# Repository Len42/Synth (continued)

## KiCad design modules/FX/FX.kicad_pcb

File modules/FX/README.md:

# Digital Effects Module

## 8HP Eurorack Module

### Features
- Chorus, echo, or plate reverb effect
- Stereo outputs
- Lighted pushbutton for tap tempo
- Uses an [Accu-Bell Effector](https://www.tubesandmore.com/sites/default/files/associated_files/p-r-abe.pdf) DSP module

### Notes
Chorus and reverb effects are stereo; echo is mono, output to both channels.

I wanted the DSP module to lie flat on the PCB so I used a right-angle socket header connector, but the connector's pins are too short so it ended up sitting at an angle:

The DSP module could be soldered directly to the PCB instead, so that it sticks out vertically.

PCB layouts are provided in KiCad and gerber formats. A PCB layout for a drilled front panel is also included.

The PCBs that I used can be ordered from OSH Park. The designs are here:
- [Front panel](https://oshpark.com/shared_projects/IcfnjVSe)
- [Controls board](https://oshpark.com/shared_projects/3NuuYXm0)
- [Main board](https://oshpark.com/shared_projects/yNs2Zlux)

Please note that I am a hobbyist, not a trained electronics engineer. No guarantees!

### Software Used

* [KiCad](https://www.kicad.org/) 6.0.8

<hr /><div><div style="float:left; padding-right:10px;"></div><div style="xfloat:left; padding-left:10px;"><br />© 2022 Len Popp CC BY<br />This work is licensed under a <a rel="license" href="http://creativecommons.org/licenses/by/4.0/">Creative Commons Attribution 4.0 International License</a>.</div></div>

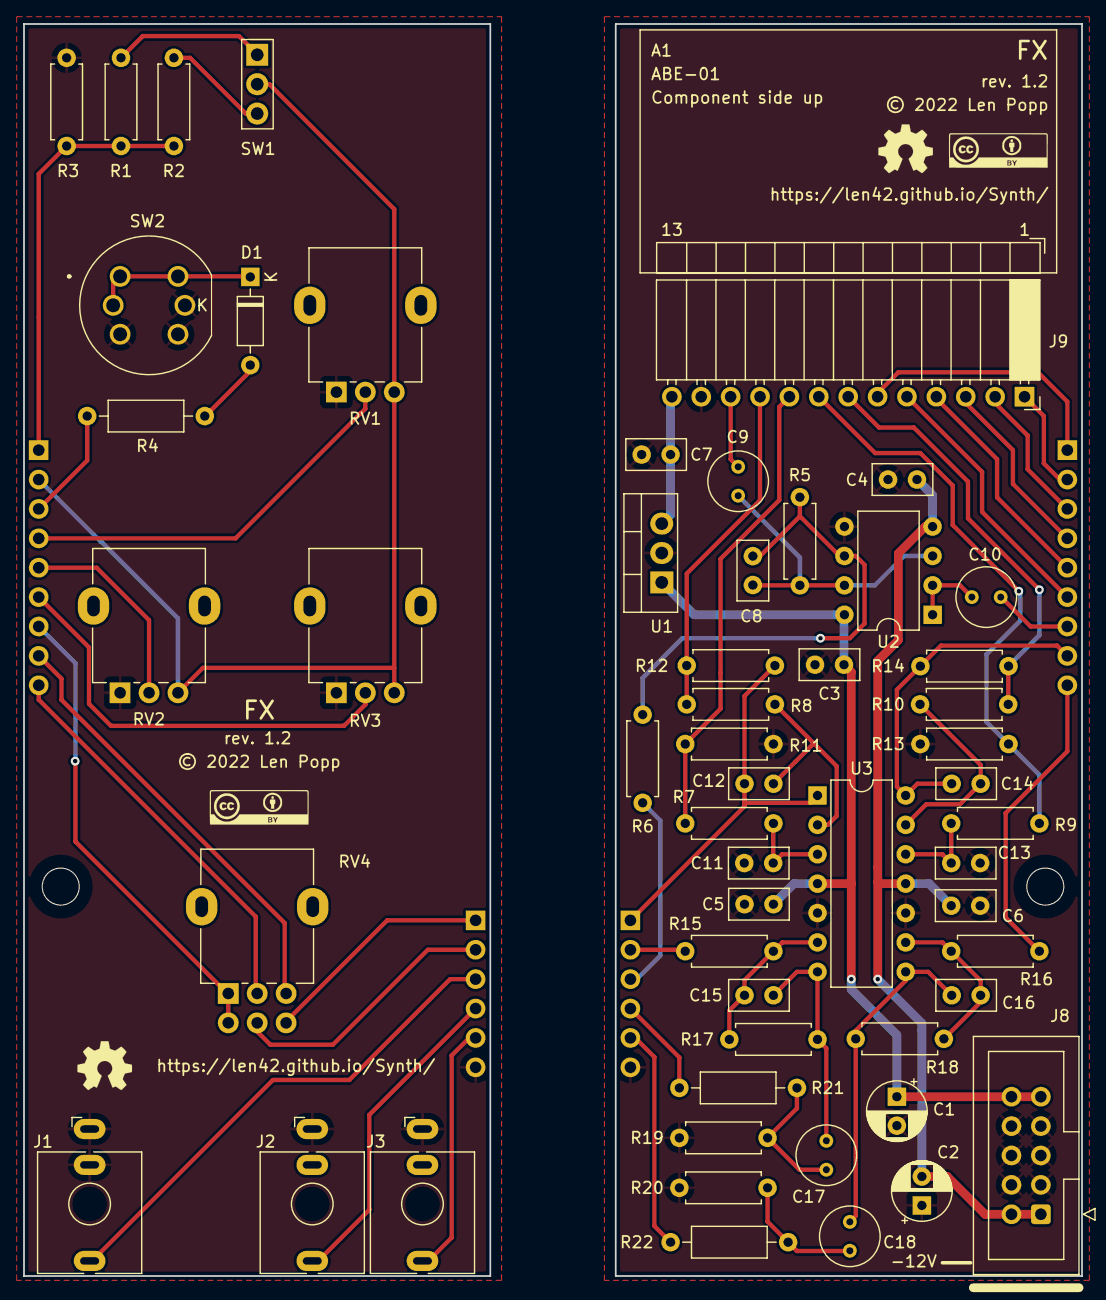
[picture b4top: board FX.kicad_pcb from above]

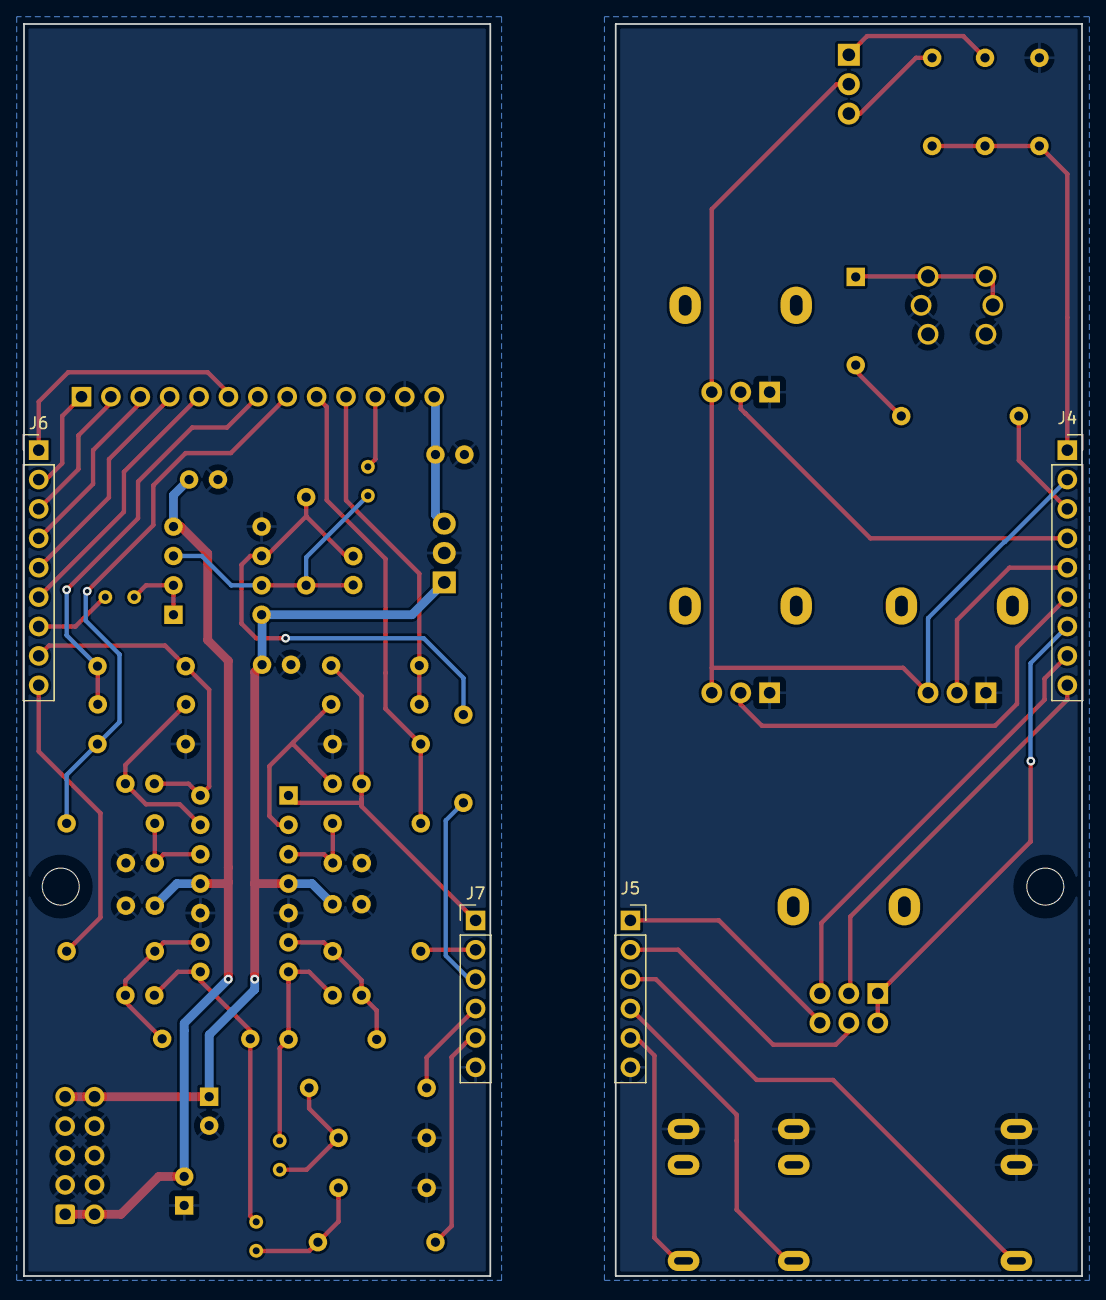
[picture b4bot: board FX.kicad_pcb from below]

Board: 2 copper layers, 91.4 x 108.2 mm, 66 parts (4 on the bottom side), 40 nets.

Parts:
A1: ABE-01; Module_ABE_Horiz_NoPads
C1, C2: 10U; CP_Radial_D5.0mm_P2.50mm
C3, C4, C5, C6, C7: 100N; C_Disc_D5.0mm_W2.5mm_P2.50mm
C8, C15, C16: 5P6; C_Disc_D5.0mm_W2.5mm_P2.50mm
C9, C10, C17, C18: 10U; C_Radial_D5.0mm_H5.0mm_P2.50mm
C11, C12, C13, C14: 470P; C_Disc_D5.0mm_W2.5mm_P2.50mm
D1: 1N4148; D_DO-35_SOD27_P7.62mm_Horizontal
G1, G2: Logo_CC_BY
G3, G4: Logo_OSHW
H2, H4: MountingHole_M3; MountingHole_PCB_3.2mm_M3
J1, J2, J3: WQP-PJ398; Jack_3.5mm_QingPu_WQP-PJ398SM_Vertical
J4: Conn_Front_Left; PinSocket_1x09_P2.54mm_Vertical
J5: Conn_Front_Right; PinSocket_1x06_P2.54mm_Vertical
J6: Conn_Back_Right; PinHeader_1x09_P2.54mm_Vertical
J7: Conn_Back_Left; PinHeader_1x06_P2.54mm_Vertical
J8: Conn_Eurorack_10; IDC-Header-Eurorack-10-TH
J9: Conn_01x13; PinSocket_1x13_P2.54mm_Horizontal
R1: 4K7; R_Axial_DIN0207_L6.3mm_D2.5mm_P7.62mm_Horizontal
R2, R3: 47K; R_Axial_DIN0207_L6.3mm_D2.5mm_P7.62mm_Horizontal
R4: 1K; R_Axial_DIN0207_L6.3mm_D2.5mm_P10.16mm_Horizontal
R5, R15, R16: 20K; R_Axial_DIN0207_L6.3mm_D2.5mm_P7.62mm_Horizontal
R6, R17, R18, R19, R20: 100K; R_Axial_DIN0207_L6.3mm_D2.5mm_P7.62mm_Horizontal
R7, R8, R9, R10: 10K; R_Axial_DIN0207_L6.3mm_D2.5mm_P7.62mm_Horizontal
R11, R12, R13, R14: 2K2; R_Axial_DIN0207_L6.3mm_D2.5mm_P7.62mm_Horizontal
R21, R22: 270R; R_Axial_DIN0207_L6.3mm_D2.5mm_P10.16mm_Horizontal
RV1, RV2, RV3: 100K; Potentiometer_Alpha_RD901F-40-00D_Single_Vertical
RV4: 100K; Potentiometer_Alpha_RD902F-40-00D_Dual_Vertical
SW1: SW_SPDT; SW_SPDT_THT_2.54
SW2: SW_Push_LED; SW_Push_LED_C&K_D6R
U1: LM7808_TO220; TO-220-3_Vertical
U2: TL072; DIP-8_W7.62mm
U3: TL074; DIP-14_W7.62mm

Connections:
+8V: C7.1, J9.13, U1.3 (VO)
+12V: C1.1, C3.1, C5.1, J8.9 (+12V), J8.10, U1.1 (VI), U2.8 (V+), U3.4 (V+)
-12V: C2.2, C4.2, C6.2, J8.1 (-12V), J8.2, U2.4 (V-), U3.11 (V-)
ABE-CTL1: J4.1, J6.1, J9.6, R1.2, R2.2, R3.1
ABE-CTL2: J4.6, J6.6, J9.5, RV3.2
ABE-CTL3: J4.5, J6.5, J9.4, RV2.2
ABE-CTL4: J4.4, J6.4, J9.3, RV1.2
ABE-CTL5: J4.3, J6.3, J9.2, R4.2
ABE-IN: C9.2, J9.11
ABE-OUT1+: J9.9, R7.1, R11.1
ABE-OUT1-: J9.10, R8.1, R12.1
ABE-OUT2+: J9.8, R9.1, R13.1
ABE-OUT2-: J9.7, R10.1, R14.1
ABE-VPOT: J4.2, J6.2, J9.1, RV1.3, RV2.3, RV3.3, SW1.2
AUDIO-IN: J1.T, J5.3, J7.3, R6.1
GND: C1.2, C2.1, C3.2, C4.1, C5.2, C6.1, C7.2, C11.2, C13.2, J1.S, J1.TN, J2.S, J3.S, J5.6, J7.6, J8.3 (GND), J8.4, J8.5 (GND), J8.6, J8.7 (GND), J8.8, J9.12, R3.2, R11.2, R13.2, R19.2, R20.2, RV1.1, RV2.1, RV3.1, SW2.3, SW2.4, SW2.6 (K), U1.2 (GND), U2.5 (+), U3.5 (+), U3.10 (+)
MIX-IN-DRY: C10.2, J4.7, J6.7, RV4.1, RV4.4
MIX-IN-WET-1: C12.2, J5.1, J7.1, R12.2, RV4.6, U3.1
MIX-IN-WET-2: C14.2, J4.8, J6.8, R14.2, RV4.3, U3.14
MIX-OUT-1: J5.2, J7.2, R15.1, RV4.5
MIX-OUT-2: J4.9, J6.9, R16.1, RV4.2
unnamed: C8.1, R5.1, R6.2, U2.6 (-)
unnamed: C8.2, C9.1, R5.2, U2.3 (+), U2.7
unnamed: C10.1, U2.1, U2.2 (-)
unnamed: C11.1, R7.2, U3.3 (+)
unnamed: C12.1, R8.2, U3.2 (-)
unnamed: C13.1, R9.2, U3.12 (+)
unnamed: C14.1, R10.2, U3.13 (-)
unnamed: C15.1, R15.2, R17.1, U3.6 (-)
unnamed: C15.2, C17.1, R17.2, U3.7
unnamed: C16.1, R16.2, R18.1, U3.9 (-)
unnamed: C16.2, C18.1, R18.2, U3.8
unnamed: C17.2, R19.1, R21.1
unnamed: C18.2, R20.1, R22.1
unnamed: D1.1 (K), SW2.1, SW2.2, SW2.5 (A)
unnamed: D1.2 (A), R4.1
unnamed: R1.1, SW1.1
unnamed: R2.1, SW1.3
OUT-1: J2.T, J5.4, J7.4, R21.2
OUT-2: J3.T, J5.5, J7.5, R22.2

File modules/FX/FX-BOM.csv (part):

Ref,Qty,Value,Value2,Note,Description,Datasheet,Manufacturer,ManuPartNum,Distributor1,DistributorPartNum1,DistributorPartLink1,Distributor2,DistributorPartNum2,DistributorPartLink2,Distributor3,DistributorPartNum3,DistributorPartLink3
"A1","1","ABE-01","","","Accu-Bell Effector digital effects module","https://www.tubesandmore.com/sites/default/files/associated_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","Accu-Bell","ABE-01","Antique Electronic Supply","P-R-ABE","https://www.tubesandmore.com/products/dsp-module-abe-accu-be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","Next Gen Guitars","BE-ABE-FX","https://nextgenguitars.ca/products/dsp-module-accu-bell-effe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","","",""
"A2","1","Cable_Eurorack_10","","Length as required","Eurorack 16-10 pin power cable","","","","Thonk","","https://www.thonk.co.uk/shop/eurorack-power-cables/","SynthCube","","https://synthcube.com/cart/eurorack-ribbon-power-cables","Modular Addict","","https://modularaddict.com/parts/eurorack-power-cables-1"
"C1 C2","2","10U","","12 V decoupling","Capacitor - Electrolytic - 12 V decoupling","https://www.mouser.ca/datasheet/2/315/ABA0000C1059-947582.pdf","Panasonic","ECE-A1VKS100I","Mouser","667-ECE-A1VKS100I","https://www.mouser.ca/ProductDetail/667-ECE-A1VKS100I","Thonk","","https://www.thonk.co.uk/shop/eurorack-diy-essentials/","","",""
"C3 C4 C5 C6 C7","5","100N","","IC decoupling","Capacitor - Ceramic - IC decoupling","https://product.tdk.com/system/files/dam/doc/product/capacit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","TDK","FG18X7R1H104KNT06","Mouser","810-FG18X7R1H104KNT6","https://www.mouser.ca/ProductDetail/810-FG18X7R1H104KNT6","","","","","",""
"C8 C15 C16","3","5P6","C0G/NP0","","Capacitor - Ceramic","https://www.mouser.ca/datasheet/2/212/KEM_C1049_GOLDMAX_C0G-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","KEMET","C315C569D1G5TA","Mouser","80-C315C569D1G","https://www.mouser.ca/ProductDetail/?qs=qe%2F8UmbcoTBh6wC284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","","","","","",""
"C9 C10 C17 C18","4","10U","","Non-polarized","Capacitor - Non-polarized Electrolytic","https://www.mouser.ca/datasheet/2/315/ABA0000C1053-947510.pdf","Panasonic","ECE-A1EN100UI","Mouser","667-ECE-A1EN100UI","https://www.mouser.ca/ProductDetail/Panasonic/ECE-A1EN100UI?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","","","","","",""
"C11 C12 C13 C14","4","470P","C0G/NP0","","Capacitor - Ceramic","https://product.tdk.com/system/files/dam/doc/product/capacit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","TDK","FA18C0G1H471JNU00","Mouser","810-FA18C0G1H47100","https://www.mouser.ca/ProductDetail/TDK/FA18C0G1H471JNU00?qs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","","","","","",""
"D1","1","1N4148","","Replace with jumper if LED is blue or white","Switching diode, 100V 0.15A, DO-35","https://www.mouser.ca/datasheet/2/308/1N914_D-2309448.pdf","On Semi / Fairchild","1N4148-T50R","Mouser","512-1N4148T50R","https://www.mouser.ca/ProductDetail/?qs=0lQeLiL1qyZS6rosZp7E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","","","","","",""
"H1 H5","2","HW_Screw_M3x0.50x6","","","Machine screw, M3x0.50x6","","","","","","","","","","","",""
"H3","1","HW_Standoff_F-F_11mm_M3x0.50","","","Standoff, 11mm, female-female, M3x0.50","https://www.thonk.co.uk/wp-content/uploads/2018/05/standoff-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","Ettinger","05.03.111","Thonk","Mech_11mm_Standoff_(x10)","https://www.thonk.co.uk/shop/standoffs/","Mouser","710-970110321","https://www.mouser.ca/ProductDetail/Wurth-Elektronik/9701103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","Mouser","144-MTS-11","https://www.mouser.ca/ProductDetail/144-MTS-11"
"J1 J2 J3","3","WQP-PJ398","","","Audio Jack, 2 Poles (Mono / TS), Switched T Pole (Normalling), QingPu / Thonkiconn","http://www.qingpu-electronics.com/en/products/WQP-PJ398SM-362.html","QingPu / Thonk","PJ398SM / WQP518MA","Thonk","PJ398SM","https://www.thonk.co.uk/shop/thonkiconn/","SynthCube","WQP518MA","https://synthcube.com/cart/3-5mm-euro-jacks","Adafruit","4031","https://www.adafruit.com/product/4031"
"J4","1","Conn_Front_Left","","","Generic connector, single row, 01x09, script generated (kicad-library-utils/schlib/autogen/connector/)","https://cdn-shop.adafruit.com/datasheets/00548.pdf","","","Adafruit","598","https://www.adafruit.com/product/598","Mouser","710-61303211821","https://www.mouser.ca/ProductDetail/Wurth-Elektronik/6130321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","","",""
"J5","1","Conn_Front_Right","","","Generic connector, single row, 01x06, script generated (kicad-library-utils/schlib/autogen/connector/)","https://cdn-shop.adafruit.com/datasheets/00548.pdf","","","Adafruit","598","https://www.adafruit.com/product/598","Mouser","710-61303211821","https://www.mouser.ca/ProductDetail/Wurth-Elektronik/6130321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","","",""
"J6","1","Conn_Back_Right","","","Generic connector, single row, 01x09, script generated (kicad-library-utils/schlib/autogen/connector/)","https://www.amphenol-icc.com/media/wysiwyg/files/documentati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","","","Adafruit","392","https://www.adafruit.com/product/392","Mouser","649-1012937893601BLF","https://www.mouser.ca/ProductDetail/649-1012937893601BLF","","",""
"J7","1","Conn_Back_Left","","","Generic connector, single row, 01x06, script generated (kicad-library-utils/schlib/autogen/connector/)","https://www.amphenol-icc.com/media/wysiwyg/files/documentati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","","","Adafruit","392","https://www.adafruit.com/product/392","Mouser","649-1012937893601BLF","https://www.mouser.ca/ProductDetail/649-1012937893601BLF","","",""
"J8","1","Conn_Eurorack_10","","","Eurorack 10-pin board power connector","https://www.mouser.ca/datasheet/2/445/61201021621-1717731.pdf","Wurth Elektronik","61201021621","Mouser","710-61201021621","https://www.mouser.ca/ProductDetail/Wurth-Elektronik/6120102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","Thonk","","https://www.thonk.co.uk/shop/eurorack-diy-essentials/","","",""
"J9","1","Conn_01x13","","Connector for module A1","Generic connector, single row, 01x13, script generated (kicad-library-utils/schlib/autogen/connector/)","https://www.mouser.ca/datasheet/2/445/613032143121-1717964.pdf","Wurth","613032143121","Mouser","710-613032143121","https://www.mouser.ca/ProductDetail/710-613032143121","","","","","",""
"R1","1","4K7","1%, 1/6 W","","Resistor","https://www.mouser.ca/datasheet/2/447/Yageo_LR_MFR_1-1714151.pdf","YAGEO","MFR-12FTF52-4K7","Mouser","603-MFR-12FTF52-4K7","https://www.mouser.ca/ProductDetail/YAGEO/MFR-12FTF52-4K7?qs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","","","","","",""
"R2 R3","2","47K","1%, 1/6 W","","Resistor","https://www.mouser.ca/datasheet/2/447/Yageo_LR_MFR_1-1714151.pdf","YAGEO","MFR-12FTF52-47K","Mouser","603-MFR-12FTF52-47K","https://www.mouser.ca/ProductDetail/YAGEO/MFR-12FTF52-47K?qs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","","","","","",""
"R4","1","1K","5%, 1/4 W","Output limiting","Resistor","https://www.mouser.ca/datasheet/2/427/ccf07-1762725.pdf","Vishay / Dale","CCF071K00JKE36","Mouser","71-CCF071K00JKE36","https://www.mouser.ca/ProductDetail/Vishay-Dale/CCF071K00JKE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","","","","","",""
"R5 R15 R16","3","20K","1%, 1/6 W","","Resistor","https://www.mouser.ca/datasheet/2/447/Yageo_LR_MFR_1-1714151.pdf","YAGEO","MFR-12FTF52-20K","Mouser","603-MFR-12FTF52-20K","https://www.mouser.ca/ProductDetail/YAGEO/MFR-12FTF52-20K?qs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","","","","","",""
"R6 R17 R18 R19 R20","5","100K","1%, 1/6 W","","Resistor","https://www.mouser.ca/datasheet/2/447/Yageo_LR_MFR_1-1714151.pdf","YAGEO","MFR-12FTF52-100K","Mouser","603-MFR-12FTF52-100K","https://www.mouser.ca/ProductDetail/YAGEO/MFR-12FTF52-100K?q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","","","","","",""
"R7 R8 R9 R10","4","10K","1%, 1/6 W","","Resistor","https://www.mouser.ca/datasheet/2/447/Yageo_LR_MFR_1-1714151.pdf","YAGEO","MFR-12FTF52-10K","Mouser","603-MFR-12FTF52-10K","https://www.mouser.ca/ProductDetail/YAGEO/MFR-12FTF52-10K?qs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","","","","","",""
"R11 R12 R13 R14","4","2K2","1%, 1/6 W","","Resistor","https://www.mouser.ca/datasheet/2/447/Yageo_LR_MFR_1-1714151.pdf","YAGEO","MFR-12FTF52-2K2","Mouser","603-MFR-12FTF52-2K2","https://www.mouser.ca/ProductDetail/YAGEO/MFR-12FTF52-2K2?qs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","","","","","",""
"R21 R22","2","270R","1%, 1/4 W","Output limiting","Resistor","https://www.mouser.ca/datasheet/2/447/Yageo_LR_MFR_1-1714151.pdf","YAGEO","MFR-25FRF52-270R","Mouser","603-MFR-25FRF52-270R","https://www.mouser.ca/ProductDetail/YAGEO/MFR-25FRF52-270R?q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","","","","","",""
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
